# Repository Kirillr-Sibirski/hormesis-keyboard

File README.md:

# Hormesis Keyboard

A custom low-profile wireless split mechanical keyboard, inspired by the Corne v3.

---

## Overview

| Spec | Detail |
|------|--------|
| Keys | 50 (split 25/25) |
| Layout | 5×6 column stagger per half + 3-key thumb cluster |
| Profile | Low-profile |
| Wireless | Bluetooth 5.0, up to 5 device profiles |
| Controller | nice!nano v2 (nRF52840) |
| RGB | WS2812 underglow, 25 LEDs per half |

---

## Repository Structure

```
hardware/
├── kicad/          KiCAD PCB schematic and layout
├── footprints/     Ergogen custom footprints
├── output/         Generated outputs (gerbers, outlines, cases)
├── top_plate/      Top plate Ergogen design
├── firmware/       Pre-built .uf2 files ready to flash
└── config.yaml     Ergogen PCB config

boards/             ZMK shield definition (hormesis_left / hormesis_right)
config/             ZMK keymap and firmware config
zephyr/             ZMK module config
build.yaml          ZMK GitHub Actions build targets
.github/workflows/  Auto-build firmware on push
```

---

## Layout

```
  1   2   3   4   5                   6   7   8   9   0
TAB   Q   W   E   R   T       Y   U   I   O   P  ESC
CAP   A   S   D   F   G       H   J   K   L   ;  SFT
  Z   X   C   V   B                   N   M   ,   .   /
                CTL ALT GUI     SPC  FN BSP
```

### Fn Layer (hold FN)

```
 F1  F2  F3  F4  F5                  F6  F7  F8  F9 F10
  `   !   @   #   $   %       ^   &   *   (   )  DEL
  _   _   -   =   [   ]      LFT DWN  UP RGT   '  ENT
BTC BT0 BT1 BT2 BT3             BT4 RGB  H+  S+   \
            USB BLE TOG     BRI EFF BOT
```

`BTC` = clear BT, `BT0–4` = select profile, `RGB` = toggle underglow, `H+/S+` = hue/saturation, `BRI` = brightness, `EFF` = next effect, `BOT` = bootloader, `USB/BLE/TOG` = output source.

---

## Flashing Firmware

Pre-built `.uf2` files are in `hardware/firmware/`:

```
hardware/firmware/hormesis_left-nice_nano_v2.uf2
hardware/firmware/hormesis_right-nice_nano_v2.uf2
```

1. Double-tap the reset button on the nice!nano — it mounts as a USB drive (`NICENANO`).
2. Drag the matching `.uf2` file onto the drive.
3. Flash left first, then right.

---

## Customizing Keymaps

**Edit the keymap** in `config/hormesis.keymap`, push to GitHub, and the Actions workflow auto-builds new firmware. Download from the Actions tab.

**ZMK Studio (GUI, no recompile):** Add `CONFIG_ZMK_STUDIO=y` to `config/hormesis.conf`, rebuild, flash, then use [zmk.studio](https://zmk.studio) to remap keys live over USB or BLE.

---

## Bill of Materials

| Part | Qty |
|------|-----|
| nice!nano v2 | 2 |
| Low-profile MX switches | 50 |
| Low-profile keycaps | 50 |
| WS2812B LEDs | 50 (25 per half) |
| SOD-123 diodes | 50 |
| JST PH 2.0 battery connector | 2 |
| LiPo battery (301230 or similar) | 2 |
| Reset switch (3×6mm SPST) | 2 |

---

## PCB Fabrication

Gerbers are in `hardware/kicad/gerber/`. Recommended fab settings:

- Layers: 2
- Thickness: 1.6 mm
- Surface finish: HASL or ENIG
- Quantity: 5 (gives 2 full keyboards + spares)

---

## License

MIT

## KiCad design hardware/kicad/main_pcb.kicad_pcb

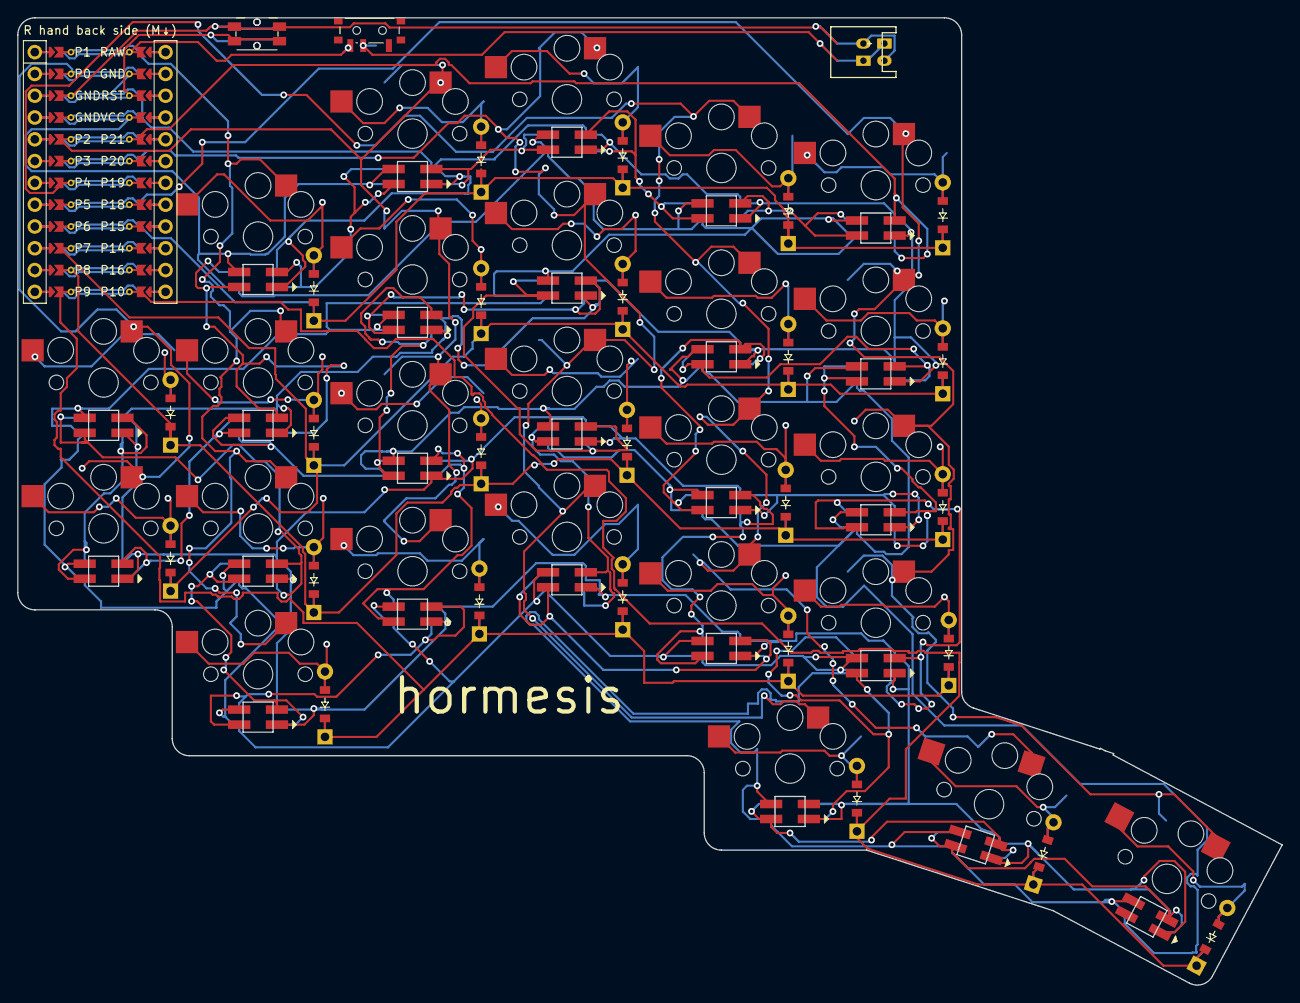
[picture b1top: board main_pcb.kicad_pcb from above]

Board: 2 copper layers, 147.4 x 112.7 mm, 81 parts (0 on the bottom side), 66 nets.

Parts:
B1, B2: Panasonic_EVQPUL_EVQPUC
D1, D2, D3, D4, D5, D6, D7, D8, D9, D10, D11, D12, D13, D14, D15, D16, D17, D18, D19, D20, D21, D22, D23, D24, D25: ComboDiode
JST1, JST2: JST_PH_S2B-PH-K_02x2.00mm_Angled
LED1, LED2, LED3, LED4, LED5, LED6, LED7, LED8, LED9, LED10, LED11, LED12, LED13, LED14, LED15, LED16, LED17, LED18, LED19, LED20, LED21, LED22, LED23, LED24, LED25: WS2812B
MCU1: mcu_supermini_nrf52840
S1, S2, S3, S4, S5, S6, S7, S8, S9, S10, S11, S12, S13, S14, S15, S16, S17, S18, S19, S20, S21, S22, S23, S24, S25: PG1350
SW1: power_switch

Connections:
GND: B1.1, B2.1, JST1.2, JST2.2, LED1.3, LED2.3, LED3.3, LED4.3, LED5.3, LED6.3, LED7.3, LED8.3, LED9.3, LED10.3, LED11.3, LED12.3, LED13.3, LED14.3, LED15.3, LED16.3, LED17.3, LED18.3, LED19.3, LED20.3, LED21.3, LED22.3, LED23.3, LED24.3, LED25.3, MCU1.102, MCU1.121, MCU1.122
P0: MCU1.123, S21.1, S22.1
P1: MCU1.124, S1.1, S2.1, S3.1, S4.1
P2: MCU1.120, S5.1, S6.1, S7.1, S8.1
P3: MCU1.119, S9.1, S10.1, S11.1, S12.1, S23.1
P4: MCU1.118, S13.1, S14.1, S15.1, S16.1, S24.1
P5: MCU1.117, S17.1, S18.1, S19.1, S20.1, S25.1
P6: D4.1, D8.1, D12.1, D16.1, D20.1, MCU1.116
P7: D3.1, D7.1, D11.1, D15.1, D19.1, D21.1, MCU1.115
P8: D2.1, D6.1, D10.1, D14.1, D18.1, D22.1, MCU1.114
P9: D1.1, D5.1, D9.1, D13.1, D17.1, MCU1.113
P10: D23.1, D24.1, D25.1, MCU1.112
P21: LED20.4, MCU1.105
RAW: MCU1.101, SW1.3, SW1.6
RST: B1.2, B2.2, MCU1.103
VCC: LED1.1, LED2.1, LED3.1, LED4.1, LED5.1, LED6.1, LED7.1, LED8.1, LED9.1, LED10.1, LED11.1, LED12.1, LED13.1, LED14.1, LED15.1, LED16.1, LED17.1, LED18.1, LED19.1, LED20.1, LED21.1, LED22.1, LED23.1, LED24.1, LED25.1, MCU1.104
main_index_bottom: D13.2, S13.2
main_index_home: D14.2, S14.2
main_index_num: D16.2, S16.2
main_index_top: D15.2, S15.2
main_inner_bottom: D17.2, S17.2
main_inner_home: D18.2, S18.2
main_inner_num: D20.2, S20.2
main_inner_top: D19.2, S19.2
main_middle_bottom: D9.2, S9.2
main_middle_home: D10.2, S10.2
main_middle_num: D12.2, S12.2
main_middle_top: D11.2, S11.2
main_pinky_bottom: D1.2, S1.2
main_pinky_home: D2.2, S2.2
main_pinky_num: D4.2, S4.2
main_pinky_top: D3.2, S3.2
main_ring_bottom: D5.2, S5.2
main_ring_home: D6.2, S6.2
main_ring_num: D8.2, S8.2
main_ring_top: D7.2, S7.2
outer_outer_home: D22.2, S22.2
outer_outer_top: D21.2, S21.2
pos: JST1.1, JST2.1, SW1.2, SW1.5
rgb_main_index_bottom: LED9.2, LED13.4
rgb_main_index_home: LED13.2, LED14.4
rgb_main_index_num: LED16.4, LED20.2
rgb_main_index_top: LED14.2, LED15.4
rgb_main_inner_bottom: LED17.4, LED18.2
rgb_main_inner_home: LED18.4, LED19.2
rgb_main_inner_top: LED15.2, LED19.4
rgb_main_middle_bottom: LED9.4, LED10.2
rgb_main_middle_home: LED10.4, LED11.2
rgb_main_middle_num: LED12.4, LED16.2
rgb_main_middle_top: LED7.2, LED11.4
rgb_main_outer_home: LED21.2, LED22.4
rgb_main_outer_top: LED3.2, LED21.4
rgb_main_pinky_bottom: LED1.4, LED2.2
rgb_main_pinky_home: LED2.4, LED22.2
rgb_main_pinky_num: LED4.4, LED8.2
rgb_main_pinky_top: LED3.4, LED4.2
rgb_main_ring_bottom: LED1.2, LED5.4
rgb_main_ring_home: LED5.2, LED6.4
rgb_main_ring_num: LED8.4, LED12.2
rgb_main_ring_top: LED6.2, LED7.4
rgb_thumbfan_far: LED24.2, LED25.4
rgb_thumbfan_home: LED23.2, LED24.4
rgb_thumbfan_near: LED17.2, LED23.4
thumbfan_far_thumb: D25.2, S25.2
thumbfan_home_thumb: D24.2, S24.2
thumbfan_near_thumb: D23.2, S23.2

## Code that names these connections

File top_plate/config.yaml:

units:
  px: cx + 2
  py: cy + 2

  pushX: (cx / 2)
  pushY: (cy / 2)

  padX: pushX + 2
  padY: pushY + 2

points:
  key.padding: cy
  zones:
    main:
      anchor:
        # Shift the PCB slightly to the right and down, otherwise it's weirdly positioned outside of the main sheet in KiCad
        shift: [100, -150]
      rows:
        bottom:
          # row_net: P9
        home:
          # row_net: P8
        top:
          # row_net: P7
        num:
          # row_net: P6
      columns:
        pinky:
          key:
            spread: cx
            bind: [16, 0, 0, 0]
            # column_net: P1
          rows:
            bottom:
              # led_in: "rgb_{{name}}"
              # led_out: rgb_main_ring_bottom
            home:
              # led_in: "rgb_{{name}}"
              # led_out: rgb_main_pinky_bottom
            top:
              # led_in: "rgb_{{name}}"
              # led_out: rgb_main_outer_top
            num:
              # led_in: "rgb_{{name}}"
              # led_out: rgb_main_pinky_top
        ring:
          key:
            stagger: 12
            spread: cx
            bind: [4, 0, 12, 0]
            # column_net: P2
          rows:
            bottom:
              # led_in: "rgb_{{name}}"
              # led_out: rgb_main_ring_home
            home:
              # led_in: "rgb_{{name}}"
              # led_out: rgb_main_ring_top
            top:
              # led_in: "rgb_{{name}}"
              # led_out: rgb_main_middle_top
            num:
              # led_in: "rgb_{{name}}"
              # led_out: rgb_main_pinky_num
        middle:
          key:
            stagger: 4
            spread: cx
            bind: [0, 0, 16, 0]
            # column_net: P3
          rows:
            bottom:
              # led_in: "rgb_{{name}}"
              # led_out: rgb_main_index_bottom
            home:
              # led_in: "rgb_{{name}}"
              # led_out: rgb_main_middle_bottom
            top:
              # led_in: "rgb_{{name}}"
              # led_out: rgb_main_middle_home
            num:
              # led_in: "rgb_{{name}}"
              # led_out: rgb_main_ring_num
        index:
          key:
            stagger: -8
            spread: cx
            bind: [8, 0, 8, 0]
            # column_net: P4
          rows:
            bottom:
              # led_in: "rgb_{{name}}"
              # led_out: rgb_main_index_home
            home:
              # led_in: "rgb_{{name}}"
              # led_out: rgb_main_index_top
            top:
              # led_in: "rgb_{{name}}"
              # led_out: rgb_main_inner_top
            num:
              # led_in: "rgb_{{name}}"
              # led_out: rgb_main_middle_num
        inner:
          key:
            stagger: -2
            spread: cx
            bind: [10, 0, 0, 0]
            # column_net: P5
          rows:
            bottom:
              # led_in: "rgb_{{name}}"
              # led_out: rgb_thumbfan_near
            home:
              # led_in: "rgb_{{name}}"
              # led_out: rgb_main_inner_bottom
            top:
              # led_in: "rgb_{{name}}"
              # led_out: rgb_main_inner_home
            num:
              # led_in: P21
              # led_out: rgb_main_index_num
    outer:
      anchor:
        ref: main_pinky_home
        shift: [-18, 0]
      columns:
        outer:
          key:
            spread: cx
            bind: [0, 0, 0, 0]
            # column_net: P0
      rows:
        top:
          # row_net: P7
          # led_in: "rgb_{{name}}"
          # led_out: rgb_main_outer_home
        home:
          # row_net: P8
          # led_in: "rgb_{{name}}"
          # led_out: rgb_main_pinky_home
    thumbfan:
      anchor:
        ref: main_inner_bottom
        shift: [-10, -17]
      columns:
        near:
          key:
            bind: [0, 3, 0, 0]
            # column_net: P3
            # led_in: "rgb_{{name}}"
            # led_out: rgb_thumbfan_home
        home:
          key:
            spread: 21
            splay: -18
            origin: [-12, -9]
            bind: [0.6, 2, 0, 4]
            # column_net: P4
            # led_in: "rgb_{{name}}"
            # led_out: rgb_thumbfan_far
        far:
          key:
            spread: 21
            splay: -10
            origin: [-10, -9]
            bind: [0.3, 0, 0, 4]
            # column_net: P5
            # led_in: "rgb_{{name}}"
            # no led_out
      rows:
        thumb:
          # row_net: P10
outlines:
  main:
    - where: true
      bound: true
      what: rectangle
      size: [cx + 2, cy + 2]
      fillet: 2
  leftkeys:
    - where: true
      what: rectangle
      size: [14, 14]
  leftcutout:
    - name: main
    - operation: subtract
      name: leftkeys

pcbs:
  main_pcb:
    outlines:
      main:
        outline: main
cases:
  plate:
    - name: leftcutout
      extrude: 1.2

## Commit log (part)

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2025-11-01 Init commit
2025-11-01 Add the basics, no adjustments yet
2025-11-02 Update pinky
2025-11-05 Reverse keyswitches, reversible promicro
2025-11-07 Positions determined (more or less)
2025-11-09 Remove mounting holes & prepare ergogen for routing
2025-11-09 Adjust positions
2025-11-21 PCB fully routed
2025-11-21 Add top plate
2026-04-26 Fix board name: nice_nano_v2 -> nice_nano/v2 for Zephyr 4.1 compat
2026-04-26 Fix board name: use nice_nano//zmk for ZMK main (Zephyr 4.1)
2026-04-26 Fix shield discovery: rename Kconfig files (capital K) and board overlays for Zephyr 4.1
2026-04-26 Remove undefined WS2812_STRIP symbol; ZMK_RGB_UNDERGLOW auto-selects LED_STRIP
2026-04-26 Add ZMK Studio key positions to physical layout
2026-04-26 Add studio_unlock combo (hold outer thumbs LCTRL+BSPC)
